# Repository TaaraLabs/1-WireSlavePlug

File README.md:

1-Wire Slave i2c bridge Plug
============================

[WebSite](https://taaralabs.eu/sp1)

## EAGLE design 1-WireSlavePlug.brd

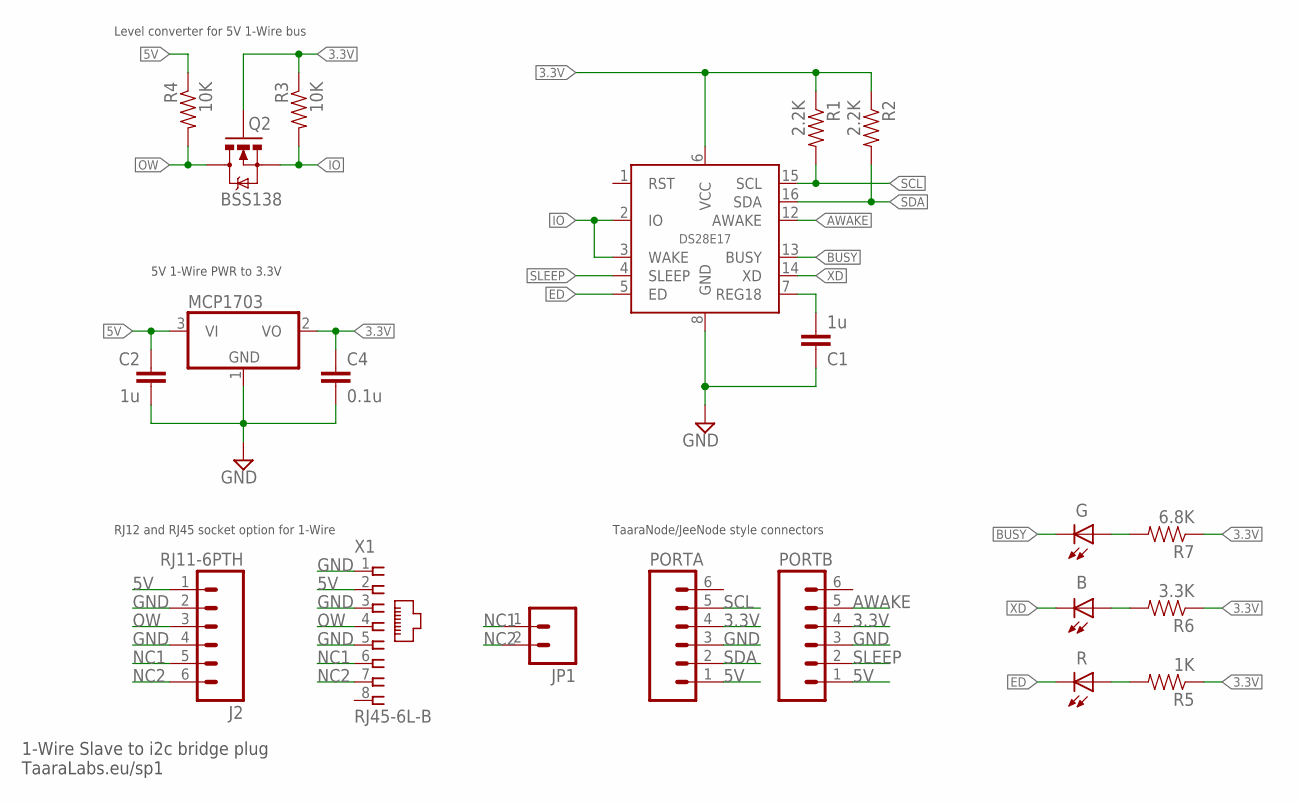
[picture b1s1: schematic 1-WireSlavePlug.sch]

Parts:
C1, C2: 1u; 0603-CAP
C4: 0.1u; 0603-CAP
IC3: MCP1703; SOT23
J2: RJ11-6PTH; RJ11-6
JP1: M02PTH; 1X02
LED: R; CHIPLED_0603
LED1: B; CHIPLED_0603
LED2: G; CHIPLED_0603
PORTA: M06SIP_LOCK; 1X06-SIP_LOCK
PORTB: M06SIP_LOCK; 1X06-SIP_LOCK
Q2: BSS138; SOT23-3
R1, R2: 2.2K; 0603-RES
R3, R4: 10K; 0603-RES
R5: 1K; 0603-RES
R6: 3.3K; 0603-RES
R7: 6.8K; 0603-RES
U$2: DS28E17; TQFN-16_4X4
X1: RJ45-6L-B; RJ45-NO-SHIELD

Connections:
3.3V: C4.1, IC3.2 (VO), PORTA.4, PORTB.4, Q2.1 (G), R1.1, R2.1, R3.1, R5.1, R6.1, R7.1, U$2.6 (VCC)
5V: C2.1, IC3.3 (VI), J2.1, PORTA.1, PORTB.1, R4.1, X1.2
AWAKE: PORTB.5, U$2.12 (AWAKE)
BUSY: LED2.C, U$2.13 (BUSY)
ED: LED.C, U$2.5 (ED)
GND: C1.1, C2.2, C4.2, IC3.1 (GND), J2.2, J2.4, PORTA.3, PORTB.3, U$2.8 (GND), X1.1, X1.3, X1.5
IO: Q2.2 (S), R3.2, U$2.2 (IO), U$2.3 (WAKE)
unnamed: C1.2, U$2.7 (REG18)
unnamed: LED.A, R5.2
unnamed: LED1.A, R6.2
unnamed: LED2.A, R7.2
NC1: J2.5, JP1.1, X1.6
NC2: J2.6, JP1.2, X1.7
OW: J2.3, Q2.3 (D), R4.2, X1.4
SCL: PORTA.5, R1.2, U$2.15 (SCL)
SDA: PORTA.2, R2.2, U$2.16 (SDA)
SLEEP: PORTB.2, U$2.4 (SLEEP)
XD: LED1.C, U$2.14 (XD)

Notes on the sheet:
1-Wire Slave to i2c bridge plug TaaraLabs.eu/sp1
Level converter for 5V 1-Wire bus
5V 1-Wire PWR to 3.3V
RJ12 and RJ45 socket option for 1-Wire
TaaraNode/JeeNode style connectors

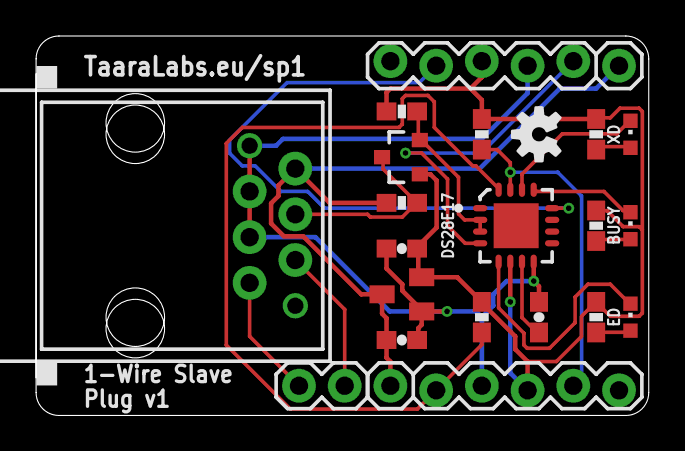
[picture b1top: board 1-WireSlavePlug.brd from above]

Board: 2 copper layers, 34.0 x 21.1 mm, 23 parts (1 on the bottom side), 18 nets.

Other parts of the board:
U$1, U$3: OSHW-LOGO-S

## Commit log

2015-10-19 :tada: Added .gitattributes & .gitignore files
2015-10-19 Initial upload
2015-10-19 README.md added
2015-10-19 Added application notes AN6208 from Maxim
2017-04-20 Added DS28E17 part Eagle Library

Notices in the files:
parts and their libraries:
SparkFun: Licensing: CC v3.0 Share-Alike You are welcome to use this library for commercial purposes.
